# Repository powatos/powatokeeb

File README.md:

# Powatokeeb

Powatokeeb is a custom mechanical keyboard designed for [Hackclub's Keeb YSWS Project](https://keeb.hackclub.com)

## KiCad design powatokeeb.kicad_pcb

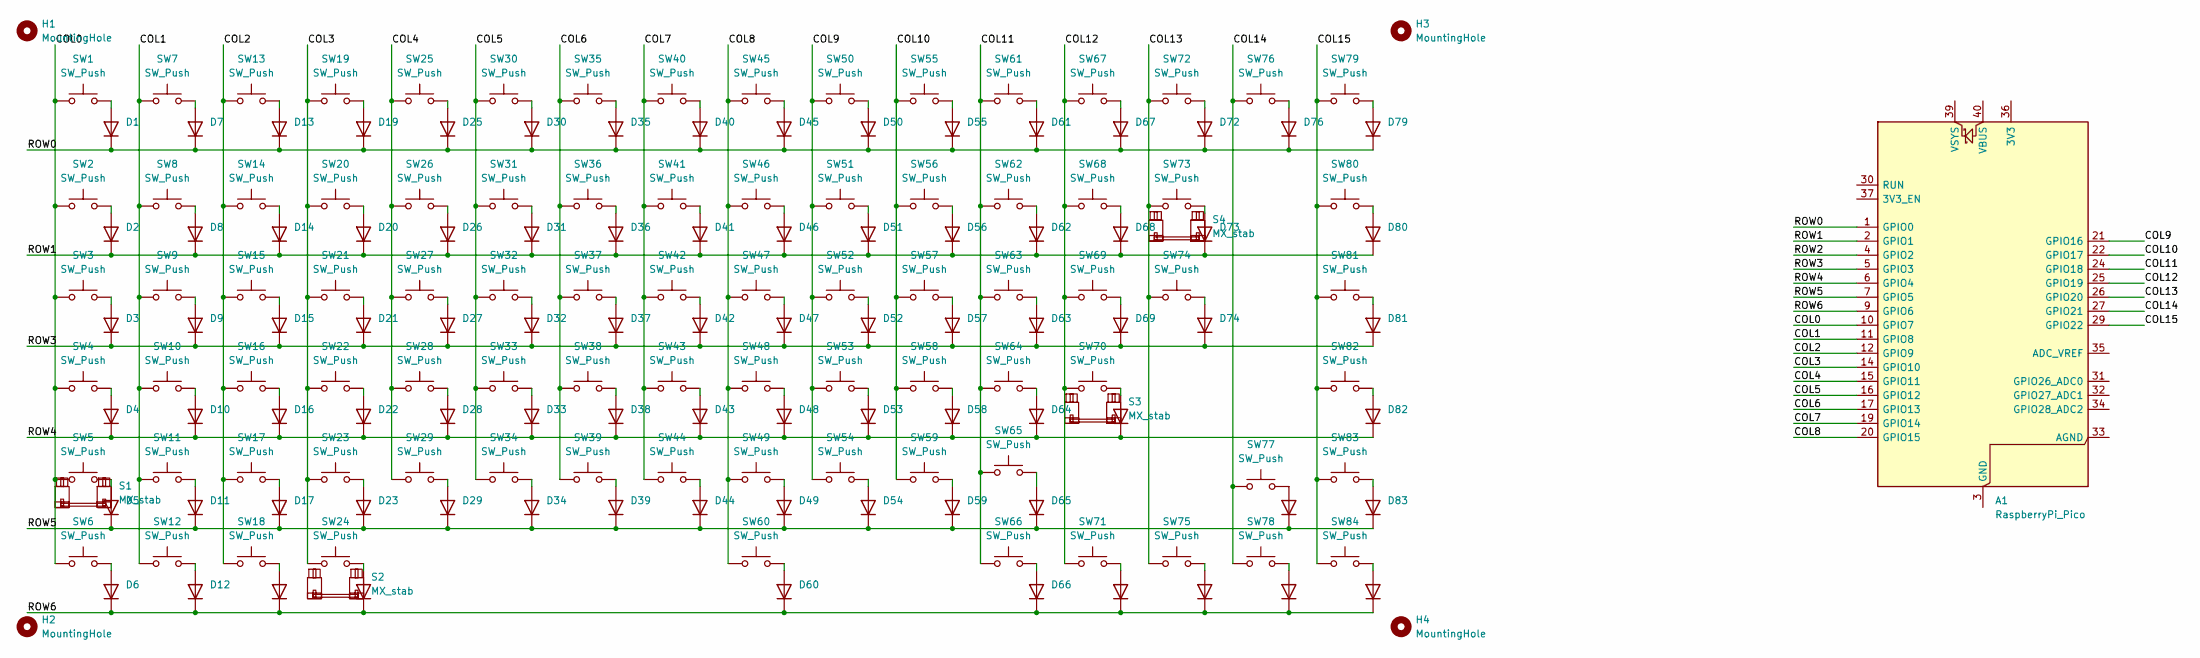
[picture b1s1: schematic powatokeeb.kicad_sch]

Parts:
A1: RaspberryPi_Pico; RaspberryPi_Pico_Common_THT
D1, D2, D3, D4, D5, D6, D7, D8, D9, D10, D11, D12, D13, D14, D15, D16, D17, D18, D19, D20, D21, D22, D23, D24, D25, D26, D27, D28, D29, D30, D31, D32, D33, D34, D35, D36, D37, D38, D39, D40, D41, D42, D43, D44, D45, D46, D47, D48, D49, D50, D51, D52, D53, D54, D55, D56, D57, D58, D59, D60, D61, D62, D63, D64, D65, D66, D67, D68, D69, D70, D71, D72, D73, D74, D75, D76, D77, D78, D79, D80, D81, D82, D83, D84: 1N4148; D_DO-35_SOD27_P7.62mm_Horizontal
H1, H2, H3, H4: MountingHole
S1, S3: MX_stab; STAB_MX_2.25u
S2: MX_stab; STAB_MX_6.25u
S4: MX_stab; STAB_MX_2u
SW1, SW2, SW5, SW7, SW8, SW9, SW10, SW11, SW13, SW14, SW15, SW16, SW17, SW19, SW20, SW21, SW22, SW23, SW24, SW25, SW26, SW27, SW28, SW29, SW30, SW31, SW32, SW33, SW34, SW35, SW36, SW37, SW38, SW39, SW40, SW41, SW42, SW43, SW44, SW45, SW46, SW47, SW48, SW49, SW50, SW51, SW52, SW53, SW54, SW55, SW56, SW57, SW58, SW59, SW60, SW61, SW62, SW63, SW64, SW66, SW67, SW68, SW69, SW70, SW71, SW72, SW73, SW75, SW76, SW77, SW78, SW79, SW80, SW81, SW82, SW83, SW84: SW_Push; SW_MX_1u
SW3, SW74: SW_Push; SW_MX_1.5u
SW4, SW65: SW_Push; SW_MX_1.75u
SW6, SW12, SW18: SW_Push; SW_MX_1.25u

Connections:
/COL0: A1.10 (GPIO7), SW1.1, SW2.1, SW3.1, SW4.1, SW5.1, SW6.1
/COL1: A1.11 (GPIO8), SW7.1, SW8.1, SW9.1, SW10.1, SW11.1, SW12.1
/COL2: A1.12 (GPIO9), SW13.1, SW14.1, SW15.1, SW16.1, SW17.1, SW18.1
/COL3: A1.14 (GPIO10), SW19.1, SW20.1, SW21.1, SW22.1, SW23.1, SW24.1
/COL4: A1.15 (GPIO11), SW25.1, SW26.1, SW27.1, SW28.1, SW29.1
/COL5: A1.16 (GPIO12), SW30.1, SW31.1, SW32.1, SW33.1, SW34.1
/COL6: A1.17 (GPIO13), SW35.1, SW36.1, SW37.1, SW38.1, SW39.1
/COL7: A1.19 (GPIO14), SW40.1, SW41.1, SW42.1, SW43.1, SW44.1
/COL8: A1.20 (GPIO15), SW45.1, SW46.1, SW47.1, SW48.1, SW49.1, SW60.1
/COL9: A1.21 (GPIO16), SW50.1, SW51.1, SW52.1, SW53.1, SW54.1
/COL10: A1.22 (GPIO17), SW55.1, SW56.1, SW57.1, SW58.1, SW59.1
/COL11: A1.24 (GPIO18), SW61.1, SW62.1, SW63.1, SW64.1, SW65.1, SW66.1
/COL12: A1.25 (GPIO19), SW67.1, SW68.1, SW69.1, SW70.1, SW71.1
/COL13: A1.26 (GPIO20), SW72.1, SW73.1, SW74.1, SW75.1
/COL14: A1.27 (GPIO21), SW76.1, SW77.1, SW78.1
/COL15: A1.29 (GPIO22), SW79.1, SW80.1, SW81.1, SW82.1, SW83.1, SW84.1
/ROW0: A1.1 (GPIO0), D1.1 (K), D7.1 (K), D13.1 (K), D19.1 (K), D25.1 (K), D30.1 (K), D35.1 (K), D40.1 (K), D45.1 (K), D50.1 (K), D55.1 (K), D61.1 (K), D67.1 (K), D72.1 (K), D76.1 (K), D79.1 (K)
/ROW1: A1.2 (GPIO1), D2.1 (K), D8.1 (K), D14.1 (K), D20.1 (K), D26.1 (K), D31.1 (K), D36.1 (K), D41.1 (K), D46.1 (K), D51.1 (K), D56.1 (K), D62.1 (K), D68.1 (K), D73.1 (K), D80.1 (K)
/ROW2: A1.4 (GPIO2)
/ROW3: A1.5 (GPIO3), D3.1 (K), D9.1 (K), D15.1 (K), D21.1 (K), D27.1 (K), D32.1 (K), D37.1 (K), D42.1 (K), D47.1 (K), D52.1 (K), D57.1 (K), D63.1 (K), D69.1 (K), D74.1 (K), D81.1 (K)
/ROW4: A1.6 (GPIO4), D4.1 (K), D10.1 (K), D16.1 (K), D22.1 (K), D28.1 (K), D33.1 (K), D38.1 (K), D43.1 (K), D48.1 (K), D53.1 (K), D58.1 (K), D64.1 (K), D70.1 (K), D82.1 (K)
/ROW5: A1.7 (GPIO5), D5.1 (K), D11.1 (K), D17.1 (K), D23.1 (K), D29.1 (K), D34.1 (K), D39.1 (K), D44.1 (K), D49.1 (K), D54.1 (K), D59.1 (K), D65.1 (K), D77.1 (K), D83.1 (K)
/ROW6: A1.9 (GPIO6), D6.1 (K), D12.1 (K), D18.1 (K), D24.1 (K), D60.1 (K), D66.1 (K), D71.1 (K), D75.1 (K), D78.1 (K), D84.1 (K)
unnamed: A1.3 (GND), A1.8 (GND), A1.13 (GND), A1.18 (GND), A1.23 (GND), A1.28 (GND), A1.38 (GND)
unnamed: D1.2 (A), SW1.2
unnamed: D2.2 (A), SW2.2
unnamed: D3.2 (A), SW3.2
unnamed: D4.2 (A), SW4.2
unnamed: D5.2 (A), SW5.2
unnamed: D6.2 (A), SW6.2
unnamed: D7.2 (A), SW7.2
unnamed: D8.2 (A), SW8.2
unnamed: D9.2 (A), SW9.2
unnamed: D10.2 (A), SW10.2
unnamed: D11.2 (A), SW11.2
unnamed: D12.2 (A), SW12.2
unnamed: D13.2 (A), SW13.2
unnamed: D14.2 (A), SW14.2
unnamed: D15.2 (A), SW15.2
unnamed: D16.2 (A), SW16.2
unnamed: D17.2 (A), SW17.2
unnamed: D18.2 (A), SW18.2
unnamed: D19.2 (A), SW19.2
unnamed: D20.2 (A), SW20.2
unnamed: D21.2 (A), SW21.2
unnamed: D22.2 (A), SW22.2
unnamed: D23.2 (A), SW23.2
unnamed: D24.2 (A), SW24.2
unnamed: D25.2 (A), SW25.2
unnamed: D26.2 (A), SW26.2
unnamed: D27.2 (A), SW27.2
unnamed: D28.2 (A), SW28.2
unnamed: D29.2 (A), SW29.2
unnamed: D30.2 (A), SW30.2
unnamed: D31.2 (A), SW31.2
unnamed: D32.2 (A), SW32.2
unnamed: D33.2 (A), SW33.2
unnamed: D34.2 (A), SW34.2
unnamed: D35.2 (A), SW35.2
unnamed: D36.2 (A), SW36.2
unnamed: D37.2 (A), SW37.2
unnamed: D38.2 (A), SW38.2
unnamed: D39.2 (A), SW39.2
unnamed: D40.2 (A), SW40.2
unnamed: D41.2 (A), SW41.2
unnamed: D42.2 (A), SW42.2
unnamed: D43.2 (A), SW43.2
unnamed: D44.2 (A), SW44.2
unnamed: D45.2 (A), SW45.2
unnamed: D46.2 (A), SW46.2
unnamed: D47.2 (A), SW47.2
unnamed: D48.2 (A), SW48.2
unnamed: D49.2 (A), SW49.2
unnamed: D50.2 (A), SW50.2
unnamed: D51.2 (A), SW51.2
unnamed: D52.2 (A), SW52.2
unnamed: D53.2 (A), SW53.2
unnamed: D54.2 (A), SW54.2
unnamed: D55.2 (A), SW55.2
unnamed: D56.2 (A), SW56.2
unnamed: D57.2 (A), SW57.2
unnamed: D58.2 (A), SW58.2
unnamed: D59.2 (A), SW59.2
unnamed: D60.2 (A), SW60.2
unnamed: D61.2 (A), SW61.2
unnamed: D62.2 (A), SW62.2
unnamed: D63.2 (A), SW63.2
unnamed: D64.2 (A), SW64.2
unnamed: D65.2 (A), SW65.2
unnamed: D66.2 (A), SW66.2
unnamed: D67.2 (A), SW67.2
unnamed: D68.2 (A), SW68.2
unnamed: D69.2 (A), SW69.2
unnamed: D70.2 (A), SW70.2
unnamed: D71.2 (A), SW71.2
unnamed: D72.2 (A), SW72.2
unnamed: D73.2 (A), SW73.2
unnamed: D74.2 (A), SW74.2
unnamed: D75.2 (A), SW75.2
unnamed: D76.2 (A), SW76.2
unnamed: D77.2 (A), SW77.2
unnamed: D78.2 (A), SW78.2
unnamed: D79.2 (A), SW79.2
unnamed: D80.2 (A), SW80.2
unnamed: D81.2 (A), SW81.2
unnamed: D82.2 (A), SW82.2
unnamed: D83.2 (A), SW83.2
unnamed: D84.2 (A), SW84.2

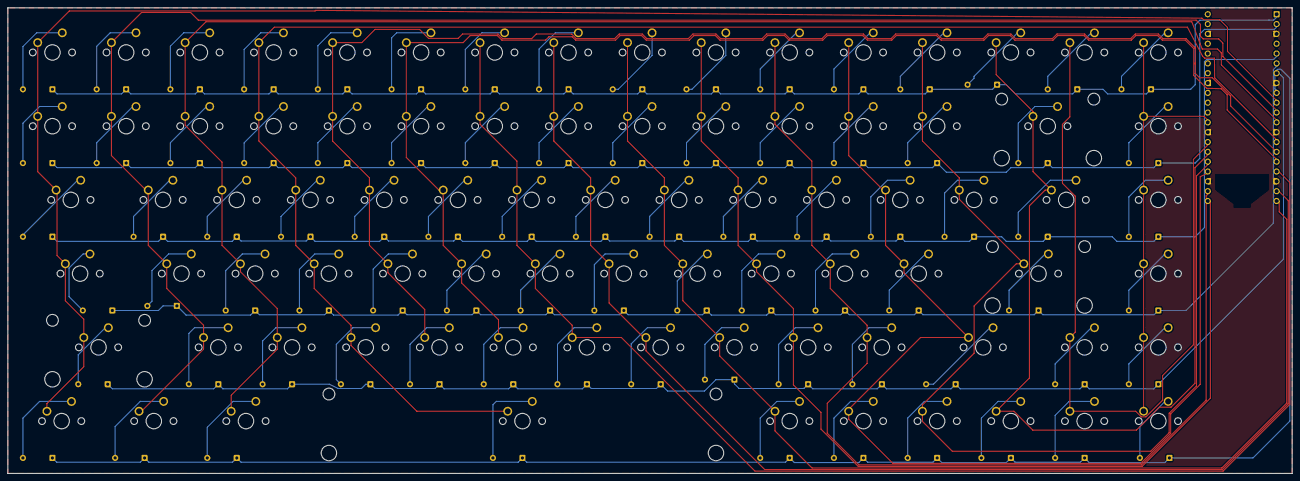
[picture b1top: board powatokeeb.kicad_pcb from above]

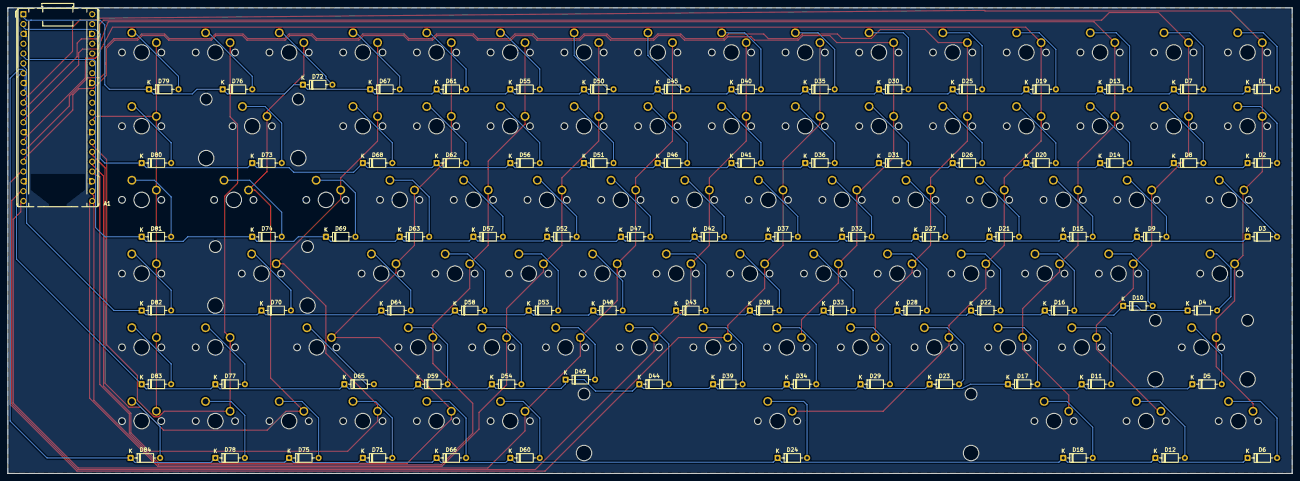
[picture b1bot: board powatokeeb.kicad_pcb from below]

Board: 2 copper layers, 331.8 x 120.3 mm, 173 parts (85 on the bottom side), 107 nets.

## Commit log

2026-06-28 6-27-2026 | Initial schematic and PCB wiring
